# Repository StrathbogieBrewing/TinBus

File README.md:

# Tinbus
A simple two wire power and data bus

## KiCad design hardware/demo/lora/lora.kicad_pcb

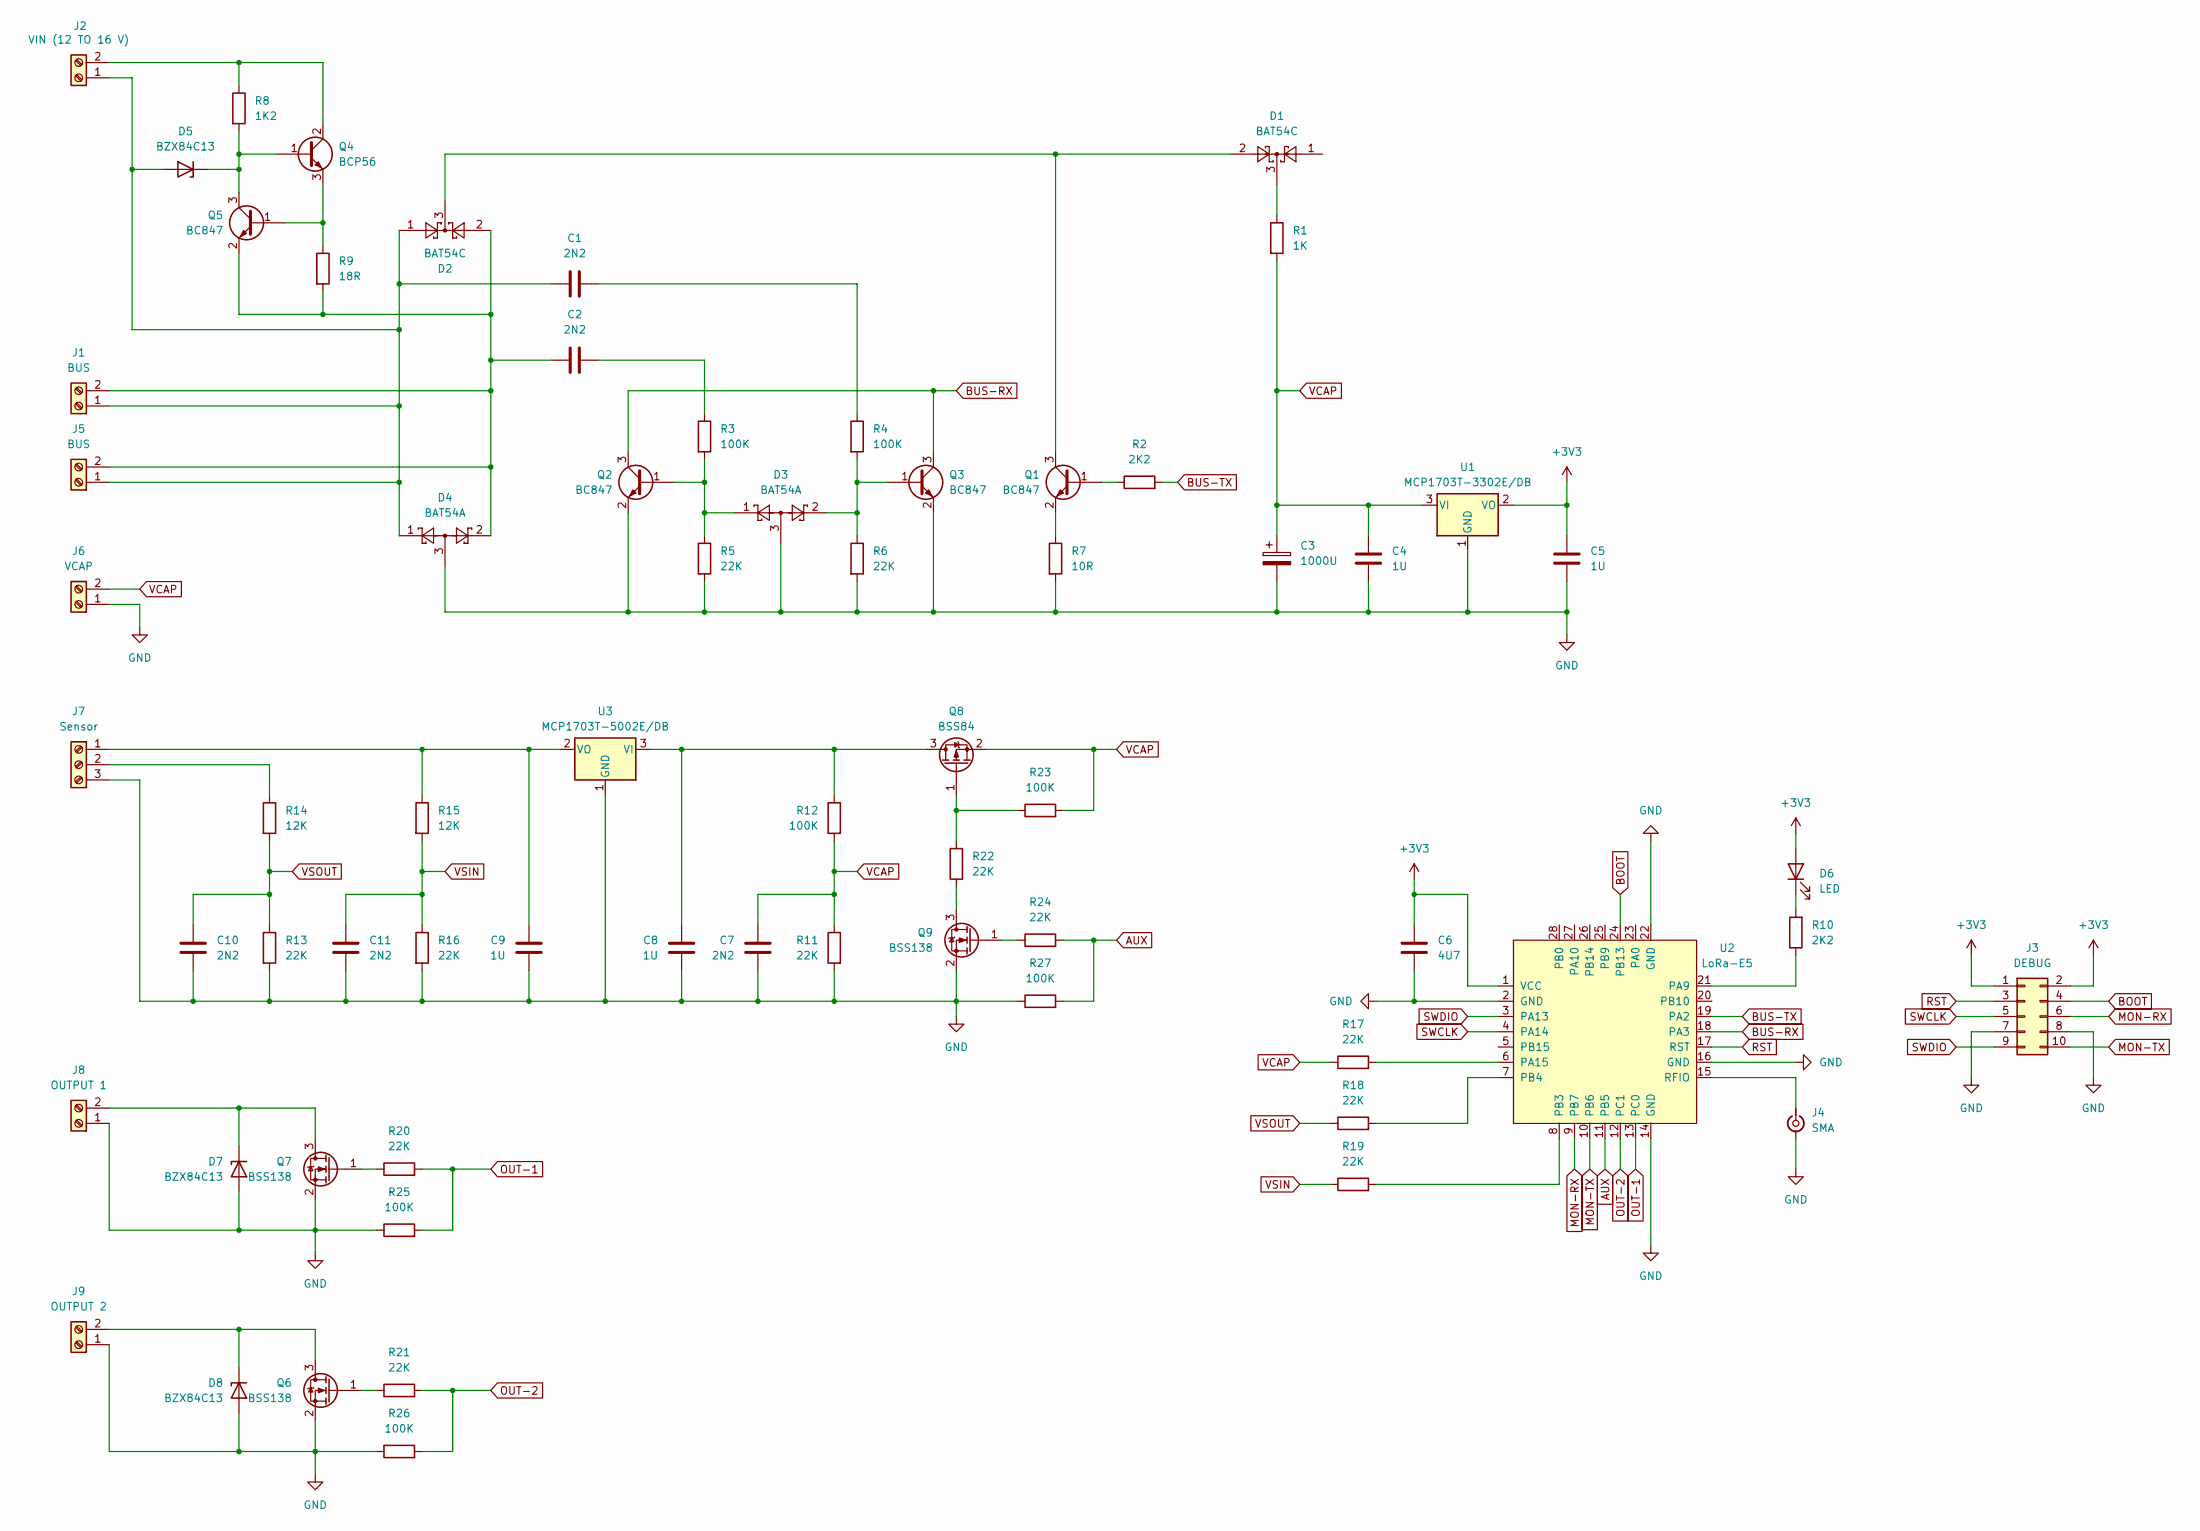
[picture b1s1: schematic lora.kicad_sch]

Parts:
C1, C2, C7, C10, C11: 2N2; C_0805_2012Metric
C3: 1000U; CP_Radial_D16.0mm_P7.50mm
C4, C5, C8, C9: 1U; C_0805_2012Metric
C6: 4U7; C_0805_2012Metric
D1, D2: BAT54C; SOT-23
D3, D4: BAT54A; SOT-23
D5, D7, D8: BZX84C13; SOT-23
D6: LED; LED_0805_2012Metric
J1, J5: BUS; TerminalBlock_bornier-2_P5.08mm
J2: VIN (12 TO 16 V); TerminalBlock_bornier-2_P5.08mm
J3: DEBUG; PinHeader_2x05_P2.54mm_Vertical
J4: SMA; SMA_Molex_73251-1153_EdgeMount_Horizontal
J6: VCAP; TerminalBlock_bornier-2_P5.08mm
J7: Sensor; TerminalBlock_bornier-3_P5.08mm
J8: OUTPUT 1; TerminalBlock_bornier-2_P5.08mm
J9: OUTPUT 2; TerminalBlock_bornier-2_P5.08mm
Q1, Q2, Q3, Q5: BC847; SOT-23
Q4: BCP56; SOT-223-3_TabPin2
Q6, Q7, Q9: BSS138; SOT-23
Q8: BSS84; SOT-23
R1: 1K; R_0805_2012Metric
R2, R10: 2K2; R_0805_2012Metric
R3, R4, R12, R23, R25, R26, R27: 100K; R_0805_2012Metric
R5, R6, R11, R13, R16, R17, R18, R19, R20, R21, R22, R24: 22K; R_0805_2012Metric
R7: 10R; R_0805_2012Metric
R8: 1K2; R_0805_2012Metric
R9: 18R; R_0805_2012Metric
R14, R15: 12K; R_0805_2012Metric
U1: MCP1703T-3302E/DB; SOT-23
U2: LoRa-E5
U3: MCP1703T-5002E/DB; SOT-23

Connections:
+3V3: C5.2, C6.2, D6.2 (A), J3.1, J3.2, U1.2 (VO), U2.1 (VCC)
AUX: R24.2, R27.2, U2.11 (PB5)
BOOT: J3.4, U2.24 (PB13~)
BUS-RX: Q2.3 (C), Q3.3 (C), U2.18 (PA3)
BUS-TX: R2.2, U2.19 (PA2)
GND: C3.2, C4.1, C5.1, C6.1, C7.1, C8.1, C9.1, C10.1, C11.1, D3.3, D4.3, D7.1 (A), D8.1 (A), J3.7, J3.8, J4.2 (Ext), J6.1, J7.3, J8.1, J9.1, Q2.2 (E), Q3.2 (E), Q6.2 (S), Q7.2 (S), Q9.2 (S), R5.2, R6.2, R7.2, R11.2, R13.2, R16.2, R25.1, R26.1, R27.1, U1.1 (GND), U2.2 (GND), U2.14 (GND), U2.16 (GND), U2.22 (GND), U3.1 (GND)
MON-RX: J3.6, U2.9 (PB7)
MON-TX: J3.10, U2.10 (PB6)
unnamed: C1.2, R4.1
unnamed: C2.2, R3.1
unnamed: D1.3, R1.1
unnamed: C1.1, D2.1, D4.1, D5.1 (A), J1.1, J2.1, J5.1
unnamed: D5.3 (K), Q4.1 (B), Q5.3 (C), R8.2
unnamed: D6.1 (K), R10.2
unnamed: D7.3 (K), J8.2, Q7.3 (D)
unnamed: D8.3 (K), J9.2, Q6.3 (D)
unnamed: C2.1, D2.2, D4.2, J1.2, J5.2, Q5.2 (E), R9.2
unnamed: J2.2, Q4.2 (C), Q4.4 (C), R8.1
unnamed: J4.1 (In), U2.15 (RFIO)
unnamed: C9.2, J7.1, R15.1, U3.2 (VO)
unnamed: J7.2, R14.1
unnamed: Q1.1 (B), R2.1
unnamed: D1.2, D2.3, Q1.3 (C)
unnamed: Q1.2 (E), R7.1
unnamed: D3.1, Q2.1 (B), R3.2, R5.1
unnamed: D3.2, Q3.1 (B), R4.2, R6.1
unnamed: Q4.3 (E), Q5.1 (B), R9.1
unnamed: Q6.1 (G), R21.1
unnamed: Q7.1 (G), R20.1
unnamed: C8.2, Q8.3 (D), R12.1, U3.3 (VI)
unnamed: Q8.1 (G), R22.2, R23.1
unnamed: Q9.3 (D), R22.1
unnamed: Q9.1 (G), R24.1
unnamed: R10.1, U2.21 (PA9)
unnamed: R17.2, U2.6 (PA15)
unnamed: R19.2, U2.8 (PB3)
unnamed: R18.2, U2.7 (PB4)
OUT-1: R20.2, R25.2, U2.13 (PC0)
OUT-2: R21.2, R26.2, U2.12 (PC1)
RST: J3.3, U2.17 (RST)
SWCLK: J3.5, U2.4 (PA14)
SWDIO: J3.9, U2.3 (PA13)
VCAP: C3.1, C4.2, C7.2, J6.2, Q8.2 (S), R1.2, R11.1, R12.2, R17.1, R23.2, U1.3 (VI)
VSIN: C11.2, R15.2, R16.1, R19.1
VSOUT: C10.2, R13.1, R14.2, R18.1

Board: 2 copper layers, 67 parts (0 on the bottom side), 45 nets, no tracks yet.

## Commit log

2021-10-04 initial import
2021-10-04 modify for more general usage and variable size payload
2021-10-04 refactor api to be more general
2021-10-05 fixed crc location
2021-10-05 periodic
2021-10-05 fixed txHoldoff
2021-10-05 working example and refactoring
2021-10-05 keywords needs tab not spaces
2021-11-16 periodic commit
2021-11-16 working tx
2021-11-16 rx working
2021-11-16 tx, rx working at 5000 bps
2021-11-17 tx is sending 4 byte frame
2021-11-18 moved old tinbus to Acebus, this is no for the new tinbus
2021-11-18 rx timing refined
2021-11-22 change dominant data pulse to zero instead of one, same as canbus
2021-12-07 temp
2021-12-07 extract hardware layer from code
2021-12-07 transmit working
2022-06-23 uart line coding
2022-08-07 cobrm tests working
2022-08-28 adding rx flow chart
2022-10-27 new version for opto
2022-10-27 rename conflicting files
2022-10-31 added opto
2022-11-27 framing works
2022-11-30 add 16 bit crc
2022-12-11 adding test framework
2024-04-03 added state diagram
2024-04-16 tinbus working
2024-06-01 added decoding sofware
2024-06-02 test results
2024-12-05 add phy simulation
2024-12-05 add lora board
2024-12-05 added pdf of simulation
2024-12-07 change to smd parts
2024-12-09 draft demo sch
2024-12-25 add polarised 5v interface
2024-12-25 add lora pcb
2024-12-25 add pdf
2024-12-26 base drive
